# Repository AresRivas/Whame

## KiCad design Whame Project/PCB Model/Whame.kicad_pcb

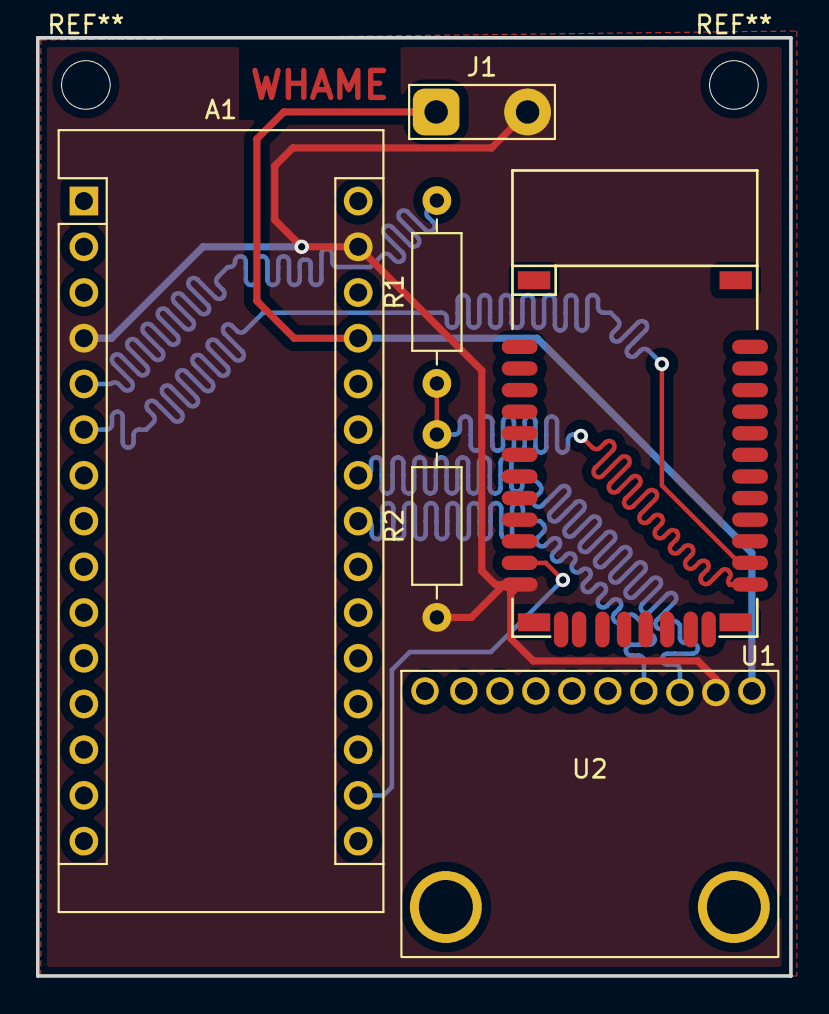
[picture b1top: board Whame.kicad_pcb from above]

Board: 2 copper layers, 41.8 x 52.1 mm, 6 parts (0 on the bottom side), 8 nets.

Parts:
A1: Arduino_Nano_Every; Arduino_Nano
J1: Conn_01x02_Female; TestPoint_2Pads_Pitch5.08mm_Drill1.3mm
R1: 10k-1/2W; R_Axial_DIN0207_L6.3mm_D2.5mm_P10.16mm_Horizontal
R2: 22k-1/2W; R_Axial_DIN0207_L6.3mm_D2.5mm_P10.16mm_Horizontal
U1: RN42
U2: MPU6050; MPU_6050_pcb

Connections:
+7.5V: A1.27 (+5V), J1.1, U2.10 (REGOUT)
GND: A1.4 (GND), A1.29 (GND), J1.2, R2.1, U1.12 (GND), U2.9 (AD0)
unnamed: A1.5 (D2), R1.2
unnamed: R1.1, R2.2, U1.13 (UART_RX)
unnamed: A1.17 (3V3), U1.11 (VDD)
unnamed: A1.6 (D3), U1.14 (UART_TX)
unnamed: A1.24 (SCL/A5), U2.8 (VLOGIC)
unnamed: A1.23 (SDA/A4), U2.7 (AUX_SCL)
